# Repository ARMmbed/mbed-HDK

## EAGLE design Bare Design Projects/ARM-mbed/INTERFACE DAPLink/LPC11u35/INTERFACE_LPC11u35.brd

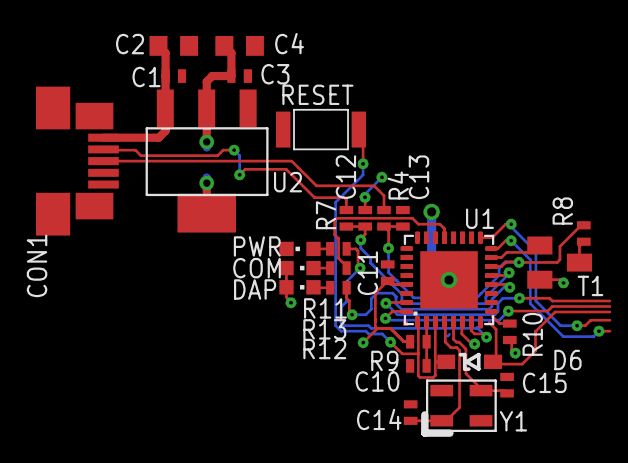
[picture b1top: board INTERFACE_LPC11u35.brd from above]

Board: 2 copper layers, 28 parts (0 on the bottom side), 21 nets.

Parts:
C1, C3, C10, C11: 100nF; 0402
C2, C4: 10uF; 0603
C12, C13, C14, C15: 18pF; 0402
CON1: 47346-0001; USB-MICRO-B-H
D6: BAT60J; SOD323
LED3: RED; CHIPLED_0603
LED4: BLUE; CHIPLED_0603
LED5: GREEN; CHIPLED_0603
R4, R7: 33R; 0402
R8, R12, R13: 1.5K; 0402
R9, R10: 10K; 0402
R11: 470R; 0402
RESET: SKRKAEE010
T1: BSS84; SOT23-3
U1: HVQFN33
U2: TLV1117LV33DCYR; SOT223
Y1: 7M-12.000MAAJ-T; 3.2X.2.5

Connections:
+3.3V: C3.1, C4.1, C11.1, LED4.A, LED5.A, R9.1, R10.1, T1.2, U1.6, U1.29, U2.OUT(1), U2.OUT(2)
GND: C1.2, C2.2, C3.2, C4.2, C10.2, C11.2, C12.2, C13.2, C14.2, C15.2, CON1.GND, LED3.C, RESET.P$1, U1.EXP, U2.GND
HID: R12.2, U1.12
IF_NRESET: C10.1, R9.2, U1.2
ISP: D6.K, RESET.P$2, U1.1, U1.3
MSD: R11.2, U1.7
unnamed: C1.1, C2.1, CON1.VBUS, U2.IN
unnamed: LED3.A, R11.1
unnamed: C13.1, R4.2, R8.2, U1.14
unnamed: C12.1, R7.2, U1.13
unnamed: T1.1, U1.15
unnamed: R8.1, T1.3
unnamed: R10.2, U1.9
unnamed: LED4.C, R12.1
unnamed: LED5.C, R13.1
unnamed: C15.1, U1.5, Y1.P$3
unnamed: C14.1, U1.4, Y1.P$1
TGT_NRESET: D6.A, U1.8
TGT_USB_D+: CON1.D+, R4.1
TGT_USB_D-: CON1.D-, R7.1
UART: R13.2, U1.21

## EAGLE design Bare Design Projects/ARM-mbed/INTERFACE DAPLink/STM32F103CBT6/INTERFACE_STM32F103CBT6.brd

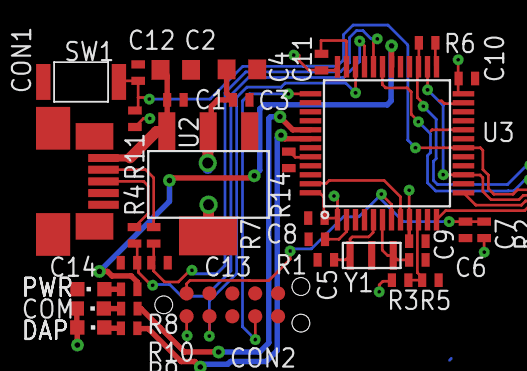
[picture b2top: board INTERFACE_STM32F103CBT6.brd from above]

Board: 2 copper layers, 35 parts (0 on the bottom side), 25 nets.

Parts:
C1, C3, C7, C8, C9, C10, C11, C12: 100nF; 0402
C2, C4: 10uF; 0603
C5, C6: 22pF; 0402
C13, C14: 18pF; 0402
CON1: 47346-0001; USB-MICRO-B-H
CON2: TC2050-IDC-NL
LED1: RED; CHIPLED_0603
LED2: BLUE; CHIPLED_0603
LED3: GREEN; CHIPLED_0603
R1, R11: 10K; 0402
R2, R14: 100K; 0402
R3, R5: 4.7K; 0402
R4, R7: 33R; 0402
R6: 100R; 0402
R8: 470R; 0402
R9, R10: 1.5K; 0402
SW1: SKRKAEE010
U2: TLV1117LV33DCYR; SOT223
U3: STM32F103CBT6; LQFP48
Y1: CSTCE8M00G55-R0

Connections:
+3.3V: C3.1, C4.1, C8.1, C9.1, C10.1, C11.1, CON2.1, LED2.A, LED3.A, R2.1, R3.1, R11.1, U2.OUT(1), U2.OUT(2), U3.1, U3.9, U3.24, U3.36, U3.48
GND: C1.2, C2.2, C3.2, C4.2, C5.2, C6.2, C7.2, C8.2, C9.2, C10.2, C11.2, C12.2, C13.2, C14.2, CON1.GND, CON2.3, CON2.5, LED1.C, R1.1, R5.2, R14.1, SW1.P$2, U2.GND, U3.8, U3.20, U3.23, U3.35, U3.47, Y1.2
IF_NRESET: C7.1, CON2.10, R2.2, U3.7
IF_SWCLK: CON2.4, U3.37
IF_SWDIO: CON2.2, U3.34
unnamed: C1.1, C2.1, CON1.VBUS, U2.IN
unnamed: R8.2, U3.30
unnamed: R14.2, U3.44
unnamed: R1.2, U3.2
unnamed: C6.1, U3.6, Y1.3
unnamed: C5.1, U3.5, Y1.1
unnamed: R3.2, R5.1, U3.10
unnamed: R9.2, U3.42
unnamed: R10.2, U3.41
unnamed: LED1.A, R8.1
unnamed: R6.1, U3.25
unnamed: LED2.C, R9.1
unnamed: LED3.C, R10.1
unnamed: C14.1, R4.1, U3.33
unnamed: C13.1, R7.1, U3.32
TGT_NRESET: C12.1, R11.2, SW1.P$1, U3.18
TGT_SWCLK: U3.15, U3.26
TGT_SWDIO: R6.2, U3.27
TGT_USB_D+: CON1.D+, R4.2
TGT_USB_D-: CON1.D-, R7.2

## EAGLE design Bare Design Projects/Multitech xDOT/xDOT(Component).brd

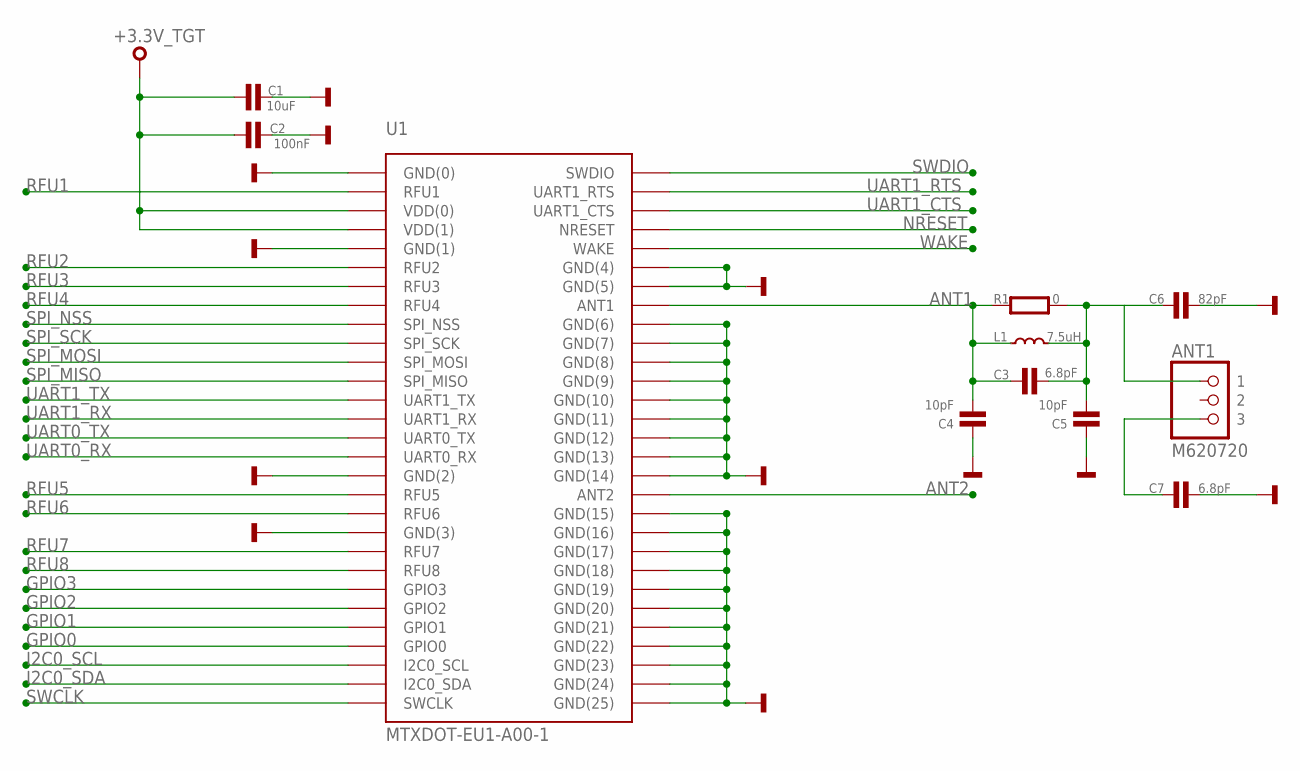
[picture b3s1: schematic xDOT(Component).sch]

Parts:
ANT1: M620720
C1: 10uF; 0603
C2: 100nF; 0603
C3, C7: 6.8pF; 0402
C4, C5: 10pF; 0402
C6: 82pF; 0402
L1: 7.5uH; 0402
R1: 0; 0402
U1: MTXDOT-EU1-A00-1; MTXDOT-EU1/NA1-A00-1

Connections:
+3.3V_TGT: C1.1, C2.1, U1.P$3 (VDD(0)), U1.P$4 (VDD(1))
ANT1: C3.1, C4.2, L1.1, R1.1, U1.P$37 (ANT1)
ANT2: U1.P$47 (ANT2)
GND: C1.2, C2.2, C4.1, C5.1, C6.1, C7.1, U1.P$1 (GND(0)), U1.P$5 (GND(1)), U1.P$17 (GND(2)), U1.P$20 (GND(3)), U1.P$35 (GND(4)), U1.P$36 (GND(5)), U1.P$38 (GND(6)), U1.P$39 (GND(7)), U1.P$40 (GND(8)), U1.P$41 (GND(9)), U1.P$42 (GND(10)), U1.P$43 (GND(11)), U1.P$44 (GND(12)), U1.P$45 (GND(13)), U1.P$46 (GND(14)), U1.P$48 (GND(15)), U1.P$49 (GND(16)), U1.P$50 (GND(17)), U1.P$51 (GND(18)), U1.P$52 (GND(19)), U1.P$53 (GND(20)), U1.P$54 (GND(21)), U1.P$55 (GND(22)), U1.P$56 (GND(23)), U1.P$57 (GND(24)), U1.P$58 (GND(25))
GPIO0: U1.P$26 (GPIO0)
GPIO1: U1.P$25 (GPIO1)
GPIO2: U1.P$24 (GPIO2)
GPIO3: U1.P$23 (GPIO3)
I2C0_SCL: U1.P$27 (I2C0_SCL)
I2C0_SDA: U1.P$28 (I2C0_SDA)
unnamed: ANT1.P$3 (3), C7.2
unnamed: ANT1.P$1 (1), C3.2, C5.2, C6.2, L1.2, R1.2
NRESET: U1.P$33 (NRESET)
RFU1: U1.P$2 (RFU1)
RFU2: U1.P$6 (RFU2)
RFU3: U1.P$7 (RFU3)
RFU4: U1.P$8 (RFU4)
RFU5: U1.P$18 (RFU5)
RFU6: U1.P$19 (RFU6)
RFU7: U1.P$21 (RFU7)
RFU8: U1.P$22 (RFU8)
SPI_MISO: U1.P$12 (SPI_MISO)
SPI_MOSI: U1.P$11 (SPI_MOSI)
SPI_NSS: U1.P$9 (SPI_NSS)
SPI_SCK: U1.P$10 (SPI_SCK)
SWCLK: U1.P$29 (SWCLK)
SWDIO: U1.P$30 (SWDIO)
UART0_RX: U1.P$16 (UART0_RX)
UART0_TX: U1.P$15 (UART0_TX)
UART1_CTS: U1.P$32 (UART1_CTS)
UART1_RTS: U1.P$31 (UART1_RTS)
UART1_RX: U1.P$14 (UART1_RX)
UART1_TX: U1.P$13 (UART1_TX)
WAKE: U1.P$34 (WAKE)

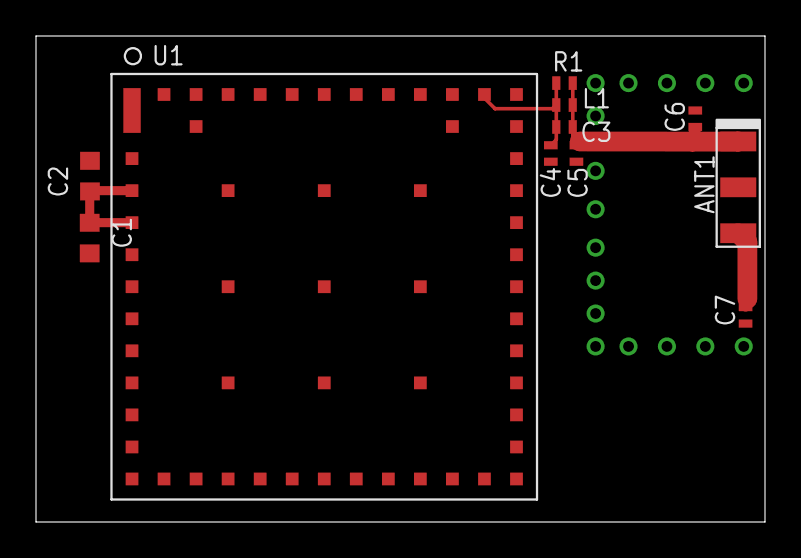
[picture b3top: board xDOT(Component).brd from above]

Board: 2 copper layers, 40.5 x 27.0 mm, 11 parts (0 on the bottom side), 5 nets.

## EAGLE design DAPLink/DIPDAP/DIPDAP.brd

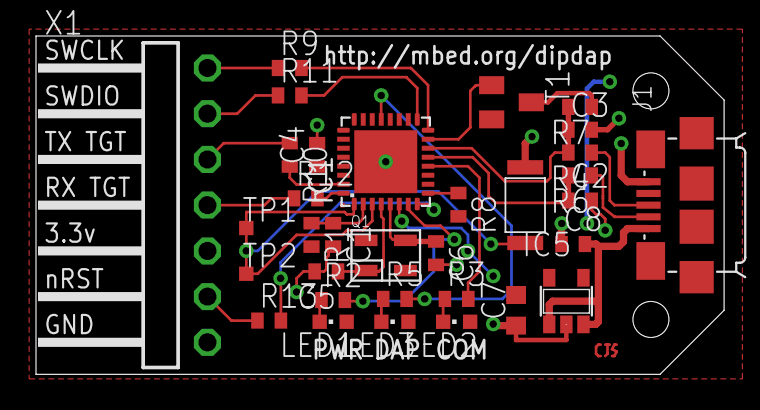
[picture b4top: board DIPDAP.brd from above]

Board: 2 copper layers, 38.2 x 18.8 mm, 33 parts (0 on the bottom side), 30 nets.

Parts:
C1, C4: 100nF; 0402
C2, C3, C5, C6: 18pF; 0402
C7: 10uF; 0603
C8: 1uF; 0402
IC1: HVQFN33
IC5: SOT23-5
J1: ZX62-B-5PA; ZX62-B-5PA(11)
LED1, LED2, LED3: RED; CHIPLED_0603
Q1: 12MHz; 3.2X.2.5
R1, R8: 10k; 0402
R2, R3, R5, R9, R10, R11, R12, R13: 470R; 0402
R4, R6: 33R; 0402
R7: 1k5; 0402
SW1: SPST_SKRKAWW010; SKRKAEE010
T1: BSS84; SOT23
TP1, TP2: TPTP08SQ; TP08SQ
X1: TSW-107-02-S-S-MBED; TSW-107-02-S-S-RA-MBED

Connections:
+3,3V: C4.1, C7.2, IC1.6, IC1.29, IC5.5, LED1.A, LED2.A, LED3.A, R1.2, R8.2, T1.2, X1.3
GND: C1.2, C2.2, C3.2, C4.2, C5.2, C6.2, C7.1, C8.1, IC1.EXP, IC5.2, J1.5, SW1.P$1, X1.1
HID: IC1.12, R3.2
IF_NRESET: C1.1, IC1.2, R1.1
ISP: IC1.1, IC1.3, SW1.P$2, TP1.TP, TP2.TP
MSD: IC1.7, R2.2
unnamed: C3.1, IC1.14, R4.2, R7.2
unnamed: C2.1, IC1.13, R6.2
unnamed: J1.2, R6.1
unnamed: J1.3, R4.1
unnamed: LED1.C, R2.1
unnamed: R7.1, T1.3
unnamed: IC1.9, R8.1
unnamed: LED2.C, R3.1
unnamed: LED3.C, R5.1
unnamed: C6.1, IC1.5, Q1.P$3
unnamed: C5.1, IC1.4, Q1.P$1
unnamed: IC1.15, T1.1
unnamed: IC1.32, R12.2
unnamed: IC1.31, R10.2
TGT_NRESET: IC1.8, R13.2
TGT_NRESET_BUF: R13.1, X1.2
TGT_RX: R12.1, X1.4
TGT_SWCLK: IC1.16, R9.2
TGT_SWCLK_BUF: R9.1, X1.7
TGT_SWDIO: IC1.17, R11.2
TGT_SWDIO_BUF: R11.1, X1.6
TGT_TX: R10.1, X1.5
UART: IC1.21, R5.2
VBUS: C8.2, IC5.1, IC5.3, J1.1

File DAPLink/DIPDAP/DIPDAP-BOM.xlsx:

Assembly | variant:
Part | Value | Device | Package | Description | Mfg | MfgPn | Disti | Order
C1 | 100nF | C0402 | 402 | Capacitor | MULTICOMP | MC0402X104K100CT | Farnell | 1759380
C2 | 18pF | C0402 | 402 | Capacitor | MULTICOMP | MC0402N180J500CT | Farnell | 1758947
C3 | 18pF | C0402 | 402 | Capacitor | MULTICOMP | MC0402N180J500CT | Farnell | 1758947
C4 | 100nF | C0402 | 402 | Capacitor | MULTICOMP | MC0402X104K100CT | Farnell | 1759380
C5 | 18pF | C0402 | 402 | Capacitor | MULTICOMP | MC0402N180J500CT | Farnell | 1758947
C6 | 18pF | C0402 | 402 | Capacitor | MULTICOMP | MC0402N180J500CT | Farnell | 1758947
C7 | 10uF | C0603 | 603 | Capacitor | MULTICOMP | MCCA000517 | Farnell | 1759393
C8 | 1uF | C0402 | 402 | Capacitor | MULTICOMP | MCCA000506 | Farnell | 1759381
IC1 | IF-LPC11U35 | HVQFN33 | NXP | LPC11U35FHI33/501 |  |  | Farnell | 2115658
IC5 | TC1014 | SOT23-5 | MICROCHIP | TC1014-3.3VCT713 |  |  | Farnell | 1331502
J1 | ZX62-B-5PA | ZX62-B-5PA | ZX62-B-5PA(11) | Hirose | ZX62-B-5PA(11) |  | Farnell | 1645325
LED1 | RED | LED0603 | CHIPLED_0603 | SMD | LED | KP-1608SURCK | Farnell | 2290329
LED2 | RED | LED0603 | CHIPLED_0603 | SMD | LED | KP-1608SURCK | Farnell | 2290329
LED3 | RED | LED0603 | CHIPLED_0603 | SMD | LED | KP-1608SURCK | Farnell | 2290329
Q1 | 12MHz | Q_3.2X2.5 | 3.2X.2.5 | TXC | 7M-12.000MAAJ-T |  | Farnell | 1842056
R1 | 10k | R0402 | 402 | Resistor | MULTICOMP | MCMR04X103-JTL | Farnell | 2072528
R2 | 470R | R0402 | 402 | Resistor | MULTICOMP | MCMR04X471-JTL | Farnell | 2073068
R3 | 470R | R0402 | 402 | Resistor | MULTICOMP | MCMR04X471-JTL | Farnell | 2073068
R4 | 33R | R0402 | 402 | Resistor | MULTICOMP | MCMR04X330-JTL | Farnell | 2072926
R5 | 470R | R0402 | 402 | Resistor | MULTICOMP | MCMR04X471-JTL | Farnell | 2073068
R6 | 33R | R0402 | 402 | Resistor | MULTICOMP | MCMR04X330-JTL | Farnell | 2072926
R7 | 1k5 | R0402 | 402 | Resistor | MULTICOMP | MCMR04X152-JTL | Farnell | 2072650
R8 | 10k | R0402 | 402 | Resistor | MULTICOMP | MCMR04X103-JTL | Farnell | 2072528
R9 | 470R | R0402 | 402 | Resistor | MULTICOMP | MCMR04X471-JTL | Farnell | 2073068
R10 | 470R | R0402 | 402 | Resistor | MULTICOMP | MCMR04X471-JTL | Farnell | 2073068
R11 | 470R | R0402 | 402 | Resistor | MULTICOMP | MCMR04X471-JTL | Farnell | 2073068
R12 | 470R | R0402 | 402 | Resistor | MULTICOMP | MCMR04X471-JTL | Farnell | 2073068
R13 | 470R | R0402 | 402 | Resistor | MULTICOMP | MCMR04X471-JTL | Farnell | 2073068
SW1 | SPST_SKRKAWW010 | SPST_SKRKAWW010 | SKRKAEE010 | Resistor | Alps | SKRKAEE010 | Mouser | 688-SKRKAE
T1 | BSS84 | BSS84 | SOT23 | P-CHANNEL | Infineon | BSS84P | Farnell | 1056526
X1 | TSW-107-02-S-S | TSW-107-02-S-S | TSW-107-02-S-S-RA | THROUGH-HOLE

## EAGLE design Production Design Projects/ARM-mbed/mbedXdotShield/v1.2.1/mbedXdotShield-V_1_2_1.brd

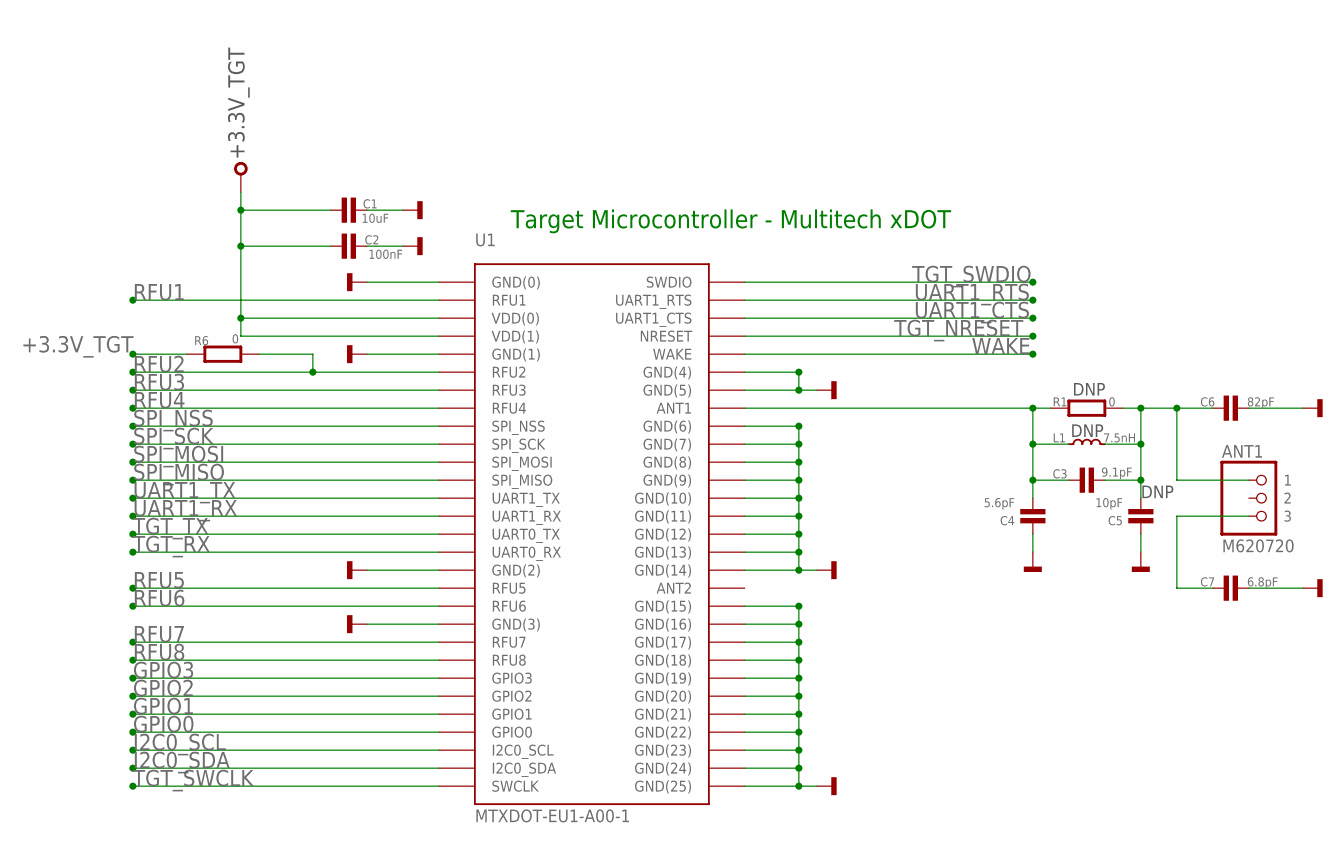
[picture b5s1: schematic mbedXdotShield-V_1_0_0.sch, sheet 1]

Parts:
ANT1: M620720
C1: 10uF; 0603
C2: 100nF; 0603
C3: 9.1pF; 0402
C4: 5.6pF; 0402
C5: 10pF; 0402
C6: 82pF; 0402
C7: 6.8pF; 0402
L1: 7.5nH; 0402
R1, R6: 0; 0402
U1: MTXDOT-EU1-A00-1; MTXDOT-EU1/NA1-A00-1

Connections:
ANT1: C3.1, C4.2, L1.1, R1.1, U1.P$37 (ANT1)
GND: C1.2, C2.2, C4.1, C5.1, C6.1, C7.1, U1.P$1 (GND(0)), U1.P$5 (GND(1)), U1.P$17 (GND(2)), U1.P$20 (GND(3)), U1.P$35 (GND(4)), U1.P$36 (GND(5)), U1.P$38 (GND(6)), U1.P$39 (GND(7)), U1.P$40 (GND(8)), U1.P$41 (GND(9)), U1.P$42 (GND(10)), U1.P$43 (GND(11)), U1.P$44 (GND(12)), U1.P$45 (GND(13)), U1.P$46 (GND(14)), U1.P$48 (GND(15)), U1.P$49 (GND(16)), U1.P$50 (GND(17)), U1.P$51 (GND(18)), U1.P$52 (GND(19)), U1.P$53 (GND(20)), U1.P$54 (GND(21)), U1.P$55 (GND(22)), U1.P$56 (GND(23)), U1.P$57 (GND(24)), U1.P$58 (GND(25)); also elsewhere on the board
GPIO0: U1.P$26 (GPIO0); also elsewhere on the board
GPIO1: U1.P$25 (GPIO1); also elsewhere on the board
GPIO2: U1.P$24 (GPIO2); also elsewhere on the board
GPIO3: U1.P$23 (GPIO3); also elsewhere on the board
I2C0_SCL: U1.P$27 (I2C0_SCL); also elsewhere on the board
I2C0_SDA: U1.P$28 (I2C0_SDA); also elsewhere on the board
unnamed: ANT1.P$3 (3), C7.2
unnamed: ANT1.P$1 (1), C3.2, C5.2, C6.2, L1.2, R1.2
RFU1: U1.P$2 (RFU1)
RFU2: R6.2, U1.P$6 (RFU2)
RFU3: U1.P$7 (RFU3)
RFU4: U1.P$8 (RFU4)
RFU5: U1.P$18 (RFU5)
RFU6: U1.P$19 (RFU6)
RFU7: U1.P$21 (RFU7)
RFU8: U1.P$22 (RFU8)
SPI_MISO: U1.P$12 (SPI_MISO); also elsewhere on the board
SPI_MOSI: U1.P$11 (SPI_MOSI); also elsewhere on the board
SPI_NSS: U1.P$9 (SPI_NSS); also elsewhere on the board
SPI_SCK: U1.P$10 (SPI_SCK); also elsewhere on the board
TGT_NRESET: U1.P$33 (NRESET); also elsewhere on the board
TGT_RX: U1.P$16 (UART0_RX); also elsewhere on the board
TGT_SWCLK: U1.P$29 (SWCLK); also elsewhere on the board
TGT_SWDIO: U1.P$30 (SWDIO); also elsewhere on the board
TGT_TX: U1.P$15 (UART0_TX); also elsewhere on the board
UART1_CTS: U1.P$32 (UART1_CTS); also elsewhere on the board
UART1_RTS: U1.P$31 (UART1_RTS); also elsewhere on the board
UART1_RX: U1.P$14 (UART1_RX); also elsewhere on the board
UART1_TX: U1.P$13 (UART1_TX); also elsewhere on the board
WAKE: U1.P$34 (WAKE); also elsewhere on the board

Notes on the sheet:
Target Microcontroller - Multitech xDOT
DNP

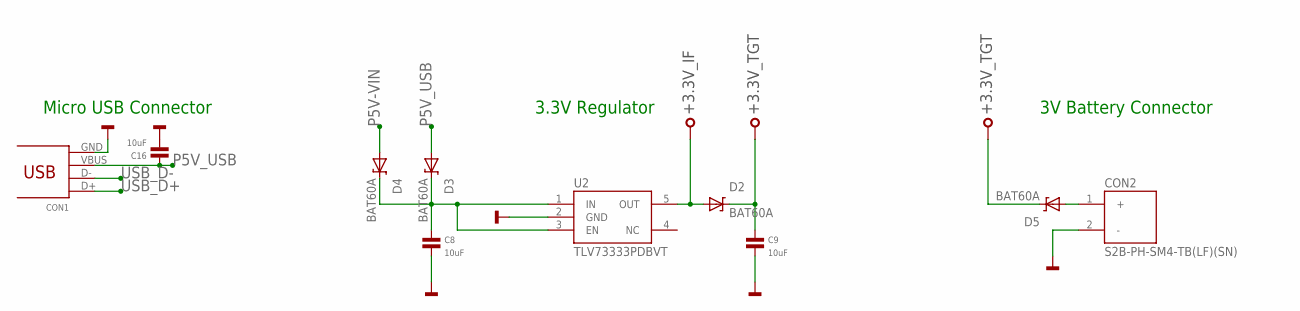
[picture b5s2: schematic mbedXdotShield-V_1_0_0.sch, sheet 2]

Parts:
C8, C9, C16: 10uF; 0603
CON1: 47346-0001; USB-MICRO-B-H
CON2: S2B-PH-SM4-TB(LF)(SN)
D2, D3, D4, D5: BAT60A; SOD323
U2: TLV73333PDBVT; SOT23-5

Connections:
GND: C8.2, C9.2, C16.2, CON1.GND, CON2.2 (-), U2.2 (GND); also elsewhere on the board
P5V-VIN: D4.A; also elsewhere on the board
P5V_USB: C16.1, CON1.VBUS, D3.A; also elsewhere on the board
USB_D+: CON1.D+; also elsewhere on the board
USB_D-: CON1.D-; also elsewhere on the board

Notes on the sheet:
3.3V Regulator
Micro USB Connector
3V Battery Connector

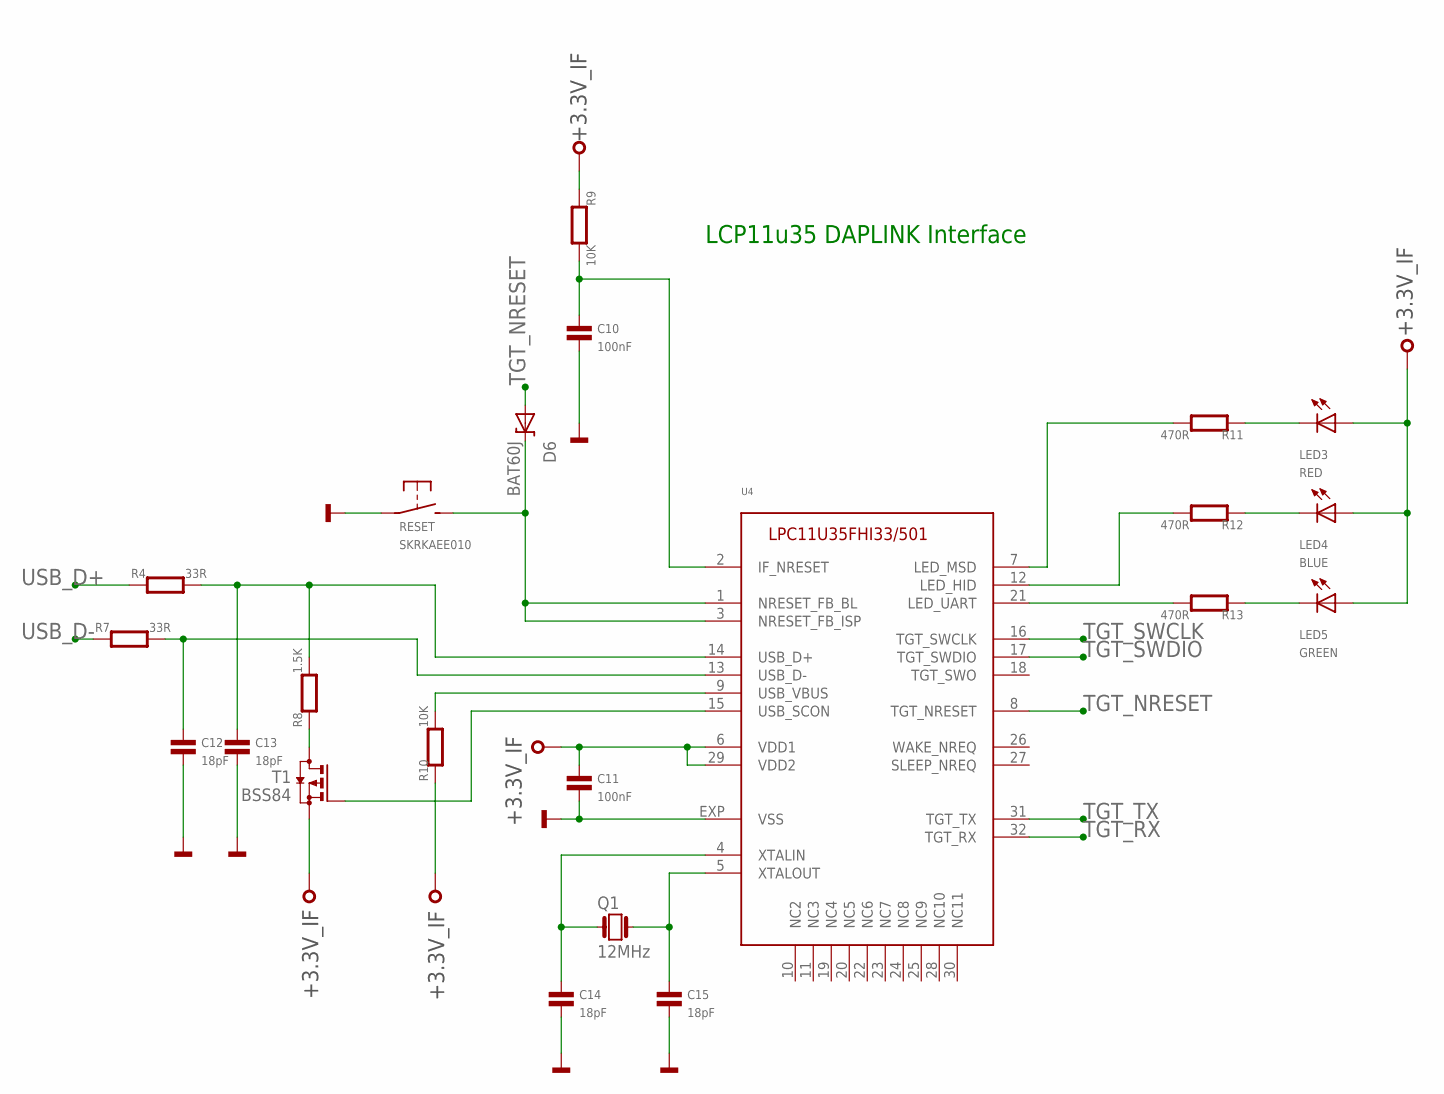
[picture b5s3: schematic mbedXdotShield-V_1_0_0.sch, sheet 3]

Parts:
C10, C11: 100nF; 0402
C12, C13, C14, C15: 18pF; 0402
D6: BAT60J; SOD323
LED3: RED; CHIPLED_0603
LED4: BLUE; CHIPLED_0603
LED5: GREEN; CHIPLED_0603
Q1: 12MHz; 3.2X.2.5
R4, R7: 33R; 0402
R8: 1.5K; 0402
R9, R10: 10K; 0402
R11, R12, R13: 470R; 0402
RESET: SKRKAEE010
T1: BSS84; SOT23-3
U4: IF-LPC11U35; HVQFN33

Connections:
GND: C10.2, C11.2, C12.2, C13.2, C14.2, C15.2, RESET.P$1, U4.EXP (VSS); also elsewhere on the board
HID: R12.2, U4.12 (LED_HID)
IF_NRESET: C10.1, R9.2, U4.2 (IF_NRESET)
ISP: D6.K, RESET.P$2 (S), U4.1 (NRESET_FB_BL), U4.3 (NRESET_FB_ISP)
MSD: R11.2, U4.7 (LED_MSD)
unnamed: C13.1, R4.2, R8.2, U4.14 (USB_D+)
unnamed: C12.1, R7.2, U4.13 (USB_D-)
unnamed: T1.1 (G), U4.15 (USB_SCON)
unnamed: R8.1, T1.3 (D)
unnamed: R10.2, U4.9 (USB_VBUS)
unnamed: LED3.C, R11.1
unnamed: LED4.C, R12.1
unnamed: LED5.C, R13.1
unnamed: C15.1, Q1.P$3 (2), U4.5 (XTALOUT)
unnamed: C14.1, Q1.P$1 (1), U4.4 (XTALIN)
TGT_NRESET: D6.A, U4.8 (TGT_NRESET); also elsewhere on the board
TGT_RX: U4.32 (TGT_RX); also elsewhere on the board
TGT_SWCLK: U4.16 (TGT_SWCLK); also elsewhere on the board
TGT_SWDIO: U4.17 (TGT_SWDIO); also elsewhere on the board
TGT_TX: U4.31 (TGT_TX); also elsewhere on the board
UART: R13.2, U4.21 (LED_UART)
USB_D+: R4.1; also elsewhere on the board
USB_D-: R7.1; also elsewhere on the board

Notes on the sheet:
LCP11u35 DAPLINK Interface

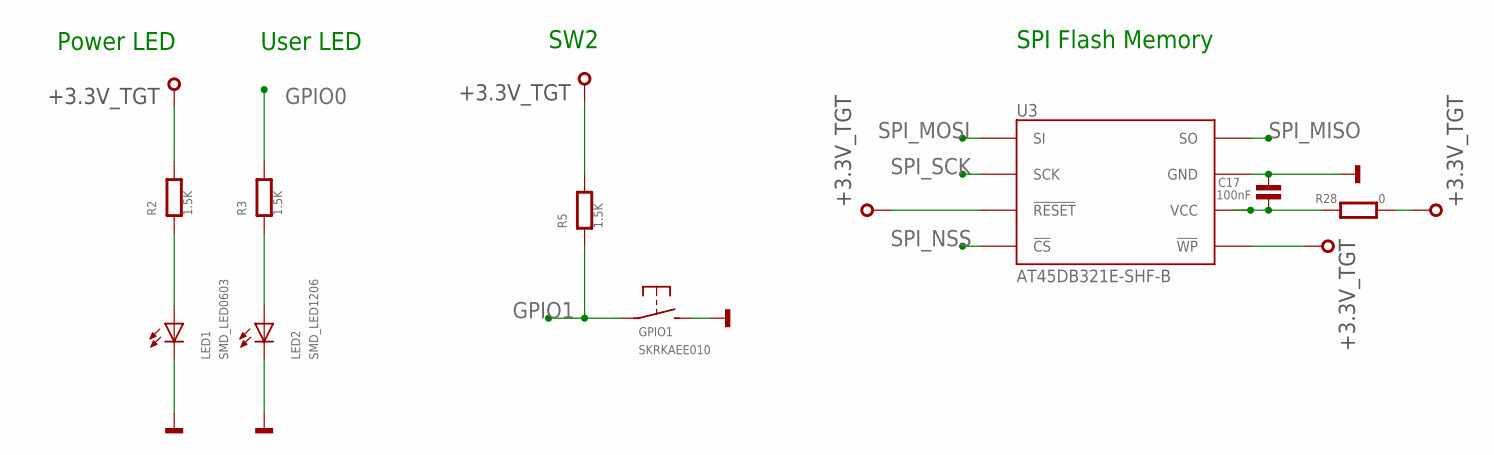
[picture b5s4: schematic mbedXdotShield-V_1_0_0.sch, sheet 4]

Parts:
C17: 100nF; 0603
GPIO1: SKRKAEE010
LED1: SMD_LED0603; CHIPLED_0603
LED2: SMD_LED1206; CHIPLED_1206
R2, R3, R5: 1.5K; 0402
R28: 0; 0402
U3: AT45DB321E-SHF-B; SO8

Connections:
GND: C17.1, GPIO1.P$2 (S), LED1.C, LED2.C, U3.7 (GND); also elsewhere on the board
GPIO0: R3.2; also elsewhere on the board
GPIO1: GPIO1.P$1, R5.1; also elsewhere on the board
unnamed: LED2.A, R3.1
unnamed: LED1.A, R2.1
unnamed: C17.2, R28.1, U3.6 (VCC)
SPI_MISO: U3.8 (SO); also elsewhere on the board
SPI_MOSI: U3.1 (SI); also elsewhere on the board
SPI_NSS: U3.4 (!CS); also elsewhere on the board
SPI_SCK: U3.2 (SCK); also elsewhere on the board

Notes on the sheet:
SW2
Power LED
User LED
SPI Flash Memory

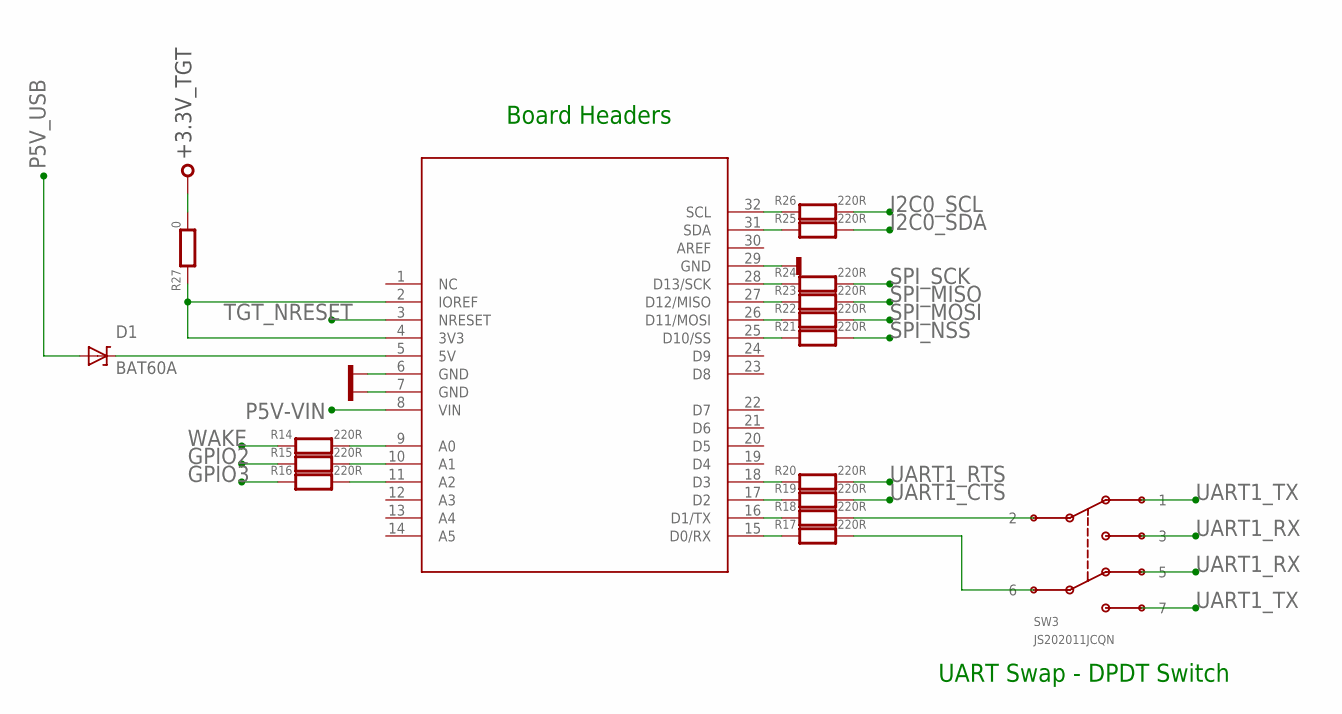
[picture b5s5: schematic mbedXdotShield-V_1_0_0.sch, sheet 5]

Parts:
BRD1: K64F/K22F-SHIELD; K64F/K22F
D1: BAT60A; SOD323
R14, R15, R16, R17, R18, R19, R20, R21, R22, R23, R24, R25, R26: 220R; 0402
R27: 0; 0402
SW3: JS202011JCQN

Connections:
GND: BRD1.6 (GND), BRD1.7 (GND), BRD1.29 (GND); also elsewhere on the board
GPIO2: R15.1; also elsewhere on the board
GPIO3: R16.1; also elsewhere on the board
I2C0_SCL: R26.2; also elsewhere on the board
I2C0_SDA: R25.2; also elsewhere on the board
unnamed: BRD1.9 (A0), R14.2
unnamed: BRD1.10 (A1), R15.2
unnamed: BRD1.11 (A2), R16.2
unnamed: BRD1.15 (D0/RX), R17.1
unnamed: BRD1.16 (D1/TX), R18.1
unnamed: BRD1.17 (D2), R19.1
unnamed: BRD1.5 (5V), D1.K
unnamed: BRD1.18 (D3), R20.1
unnamed: BRD1.25 (D10/SS), R21.1
unnamed: BRD1.26 (D11/MOSI), R22.1
unnamed: BRD1.27 (D12/MISO), R23.1
unnamed: BRD1.28 (D13/SCK), R24.1
unnamed: BRD1.31 (SDA), R25.1
unnamed: BRD1.32 (SCL), R26.1
unnamed: BRD1.2 (IOREF), BRD1.4 (3V3), R27.1
unnamed: R17.2, SW3.6
unnamed: R18.2, SW3.2
P5V-VIN: BRD1.8 (VIN); also elsewhere on the board
P5V_USB: D1.A; also elsewhere on the board
SPI_MISO: R23.2; also elsewhere on the board
SPI_MOSI: R22.2; also elsewhere on the board
SPI_NSS: R21.2; also elsewhere on the board
SPI_SCK: R24.2; also elsewhere on the board
TGT_NRESET: BRD1.3 (NRESET); also elsewhere on the board
UART1_CTS: R19.2; also elsewhere on the board
UART1_RTS: R20.2; also elsewhere on the board
UART1_RX: SW3.3, SW3.5; also elsewhere on the board
UART1_TX: SW3.1, SW3.7; also elsewhere on the board
WAKE: R14.1; also elsewhere on the board

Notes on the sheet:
Board Headers
UART Swap - DPDT Switch

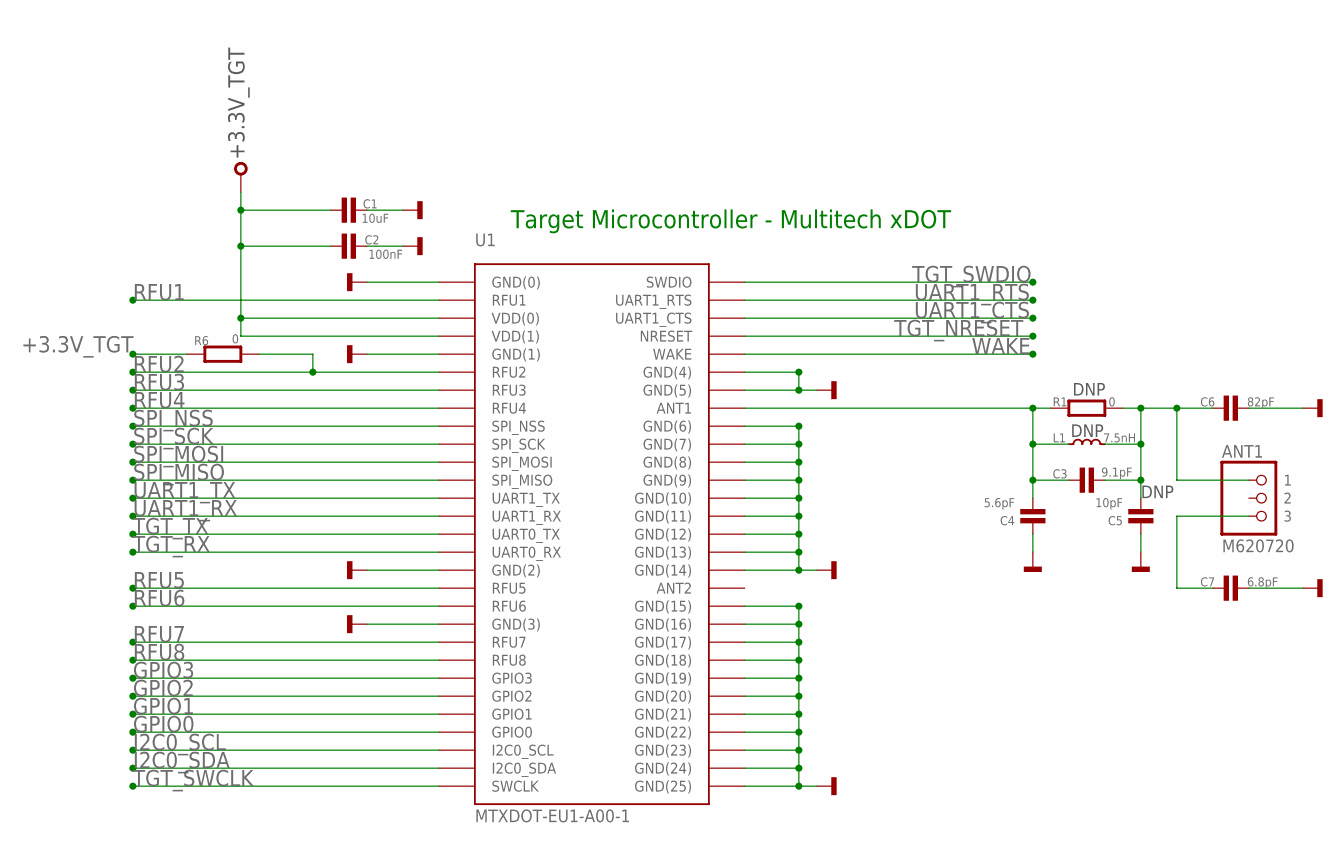
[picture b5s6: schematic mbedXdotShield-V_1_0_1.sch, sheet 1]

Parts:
ANT1: M620720
C1: 10uF; 0603
C2: 100nF; 0603
C3: 9.1pF; 0402
C4: 5.6pF; 0402
C5: 10pF; 0402
C6: 82pF; 0402
C7: 6.8pF; 0402
L1: 7.5nH; 0402
R1, R6: 0; 0402
U1: MTXDOT-EU1-A00-1; MTXDOT-EU1/NA1-A00-1

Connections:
ANT1: C3.1, C4.2, L1.1, R1.1, U1.P$37 (ANT1)
GND: C1.2, C2.2, C4.1, C5.1, C6.1, C7.1, U1.P$1 (GND(0)), U1.P$5 (GND(1)), U1.P$17 (GND(2)), U1.P$20 (GND(3)), U1.P$35 (GND(4)), U1.P$36 (GND(5)), U1.P$38 (GND(6)), U1.P$39 (GND(7)), U1.P$40 (GND(8)), U1.P$41 (GND(9)), U1.P$42 (GND(10)), U1.P$43 (GND(11)), U1.P$44 (GND(12)), U1.P$45 (GND(13)), U1.P$46 (GND(14)), U1.P$48 (GND(15)), U1.P$49 (GND(16)), U1.P$50 (GND(17)), U1.P$51 (GND(18)), U1.P$52 (GND(19)), U1.P$53 (GND(20)), U1.P$54 (GND(21)), U1.P$55 (GND(22)), U1.P$56 (GND(23)), U1.P$57 (GND(24)), U1.P$58 (GND(25)); also elsewhere on the board
GPIO0: U1.P$26 (GPIO0); also elsewhere on the board
GPIO1: U1.P$25 (GPIO1); also elsewhere on the board
GPIO2: U1.P$24 (GPIO2); also elsewhere on the board
GPIO3: U1.P$23 (GPIO3); also elsewhere on the board
I2C0_SCL: U1.P$27 (I2C0_SCL); also elsewhere on the board
I2C0_SDA: U1.P$28 (I2C0_SDA); also elsewhere on the board
unnamed: ANT1.P$3 (3), C7.2
unnamed: ANT1.P$1 (1), C3.2, C5.2, C6.2, L1.2, R1.2
RFU1: U1.P$2 (RFU1)
RFU2: R6.2, U1.P$6 (RFU2)
RFU3: U1.P$7 (RFU3)
RFU4: U1.P$8 (RFU4)
RFU5: U1.P$18 (RFU5)
RFU6: U1.P$19 (RFU6)
RFU7: U1.P$21 (RFU7)
RFU8: U1.P$22 (RFU8)
SPI_MISO: U1.P$12 (SPI_MISO); also elsewhere on the board
SPI_MOSI: U1.P$11 (SPI_MOSI); also elsewhere on the board
SPI_NSS: U1.P$9 (SPI_NSS); also elsewhere on the board
SPI_SCK: U1.P$10 (SPI_SCK); also elsewhere on the board
TGT_NRESET: U1.P$33 (NRESET); also elsewhere on the board
TGT_RX: U1.P$16 (UART0_RX); also elsewhere on the board
TGT_SWCLK: U1.P$29 (SWCLK); also elsewhere on the board
TGT_SWDIO: U1.P$30 (SWDIO); also elsewhere on the board
TGT_TX: U1.P$15 (UART0_TX); also elsewhere on the board
UART1_CTS: U1.P$32 (UART1_CTS); also elsewhere on the board
UART1_RTS: U1.P$31 (UART1_RTS); also elsewhere on the board
UART1_RX: U1.P$14 (UART1_RX); also elsewhere on the board
UART1_TX: U1.P$13 (UART1_TX); also elsewhere on the board
WAKE: U1.P$34 (WAKE); also elsewhere on the board

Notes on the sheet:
Target Microcontroller - Multitech xDOT
DNP

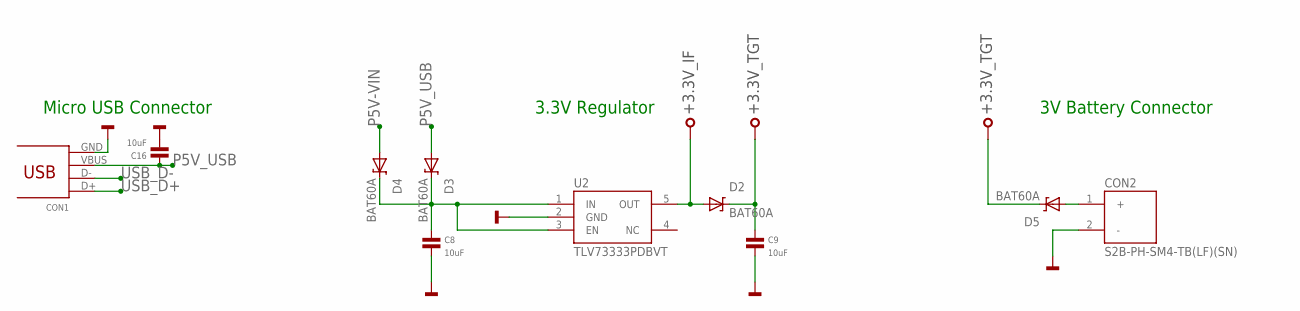
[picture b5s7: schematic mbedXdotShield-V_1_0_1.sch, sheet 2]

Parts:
C8, C9, C16: 10uF; 0603
CON1: 47346-0001; USB-MICRO-B-H
CON2: S2B-PH-SM4-TB(LF)(SN)
D2, D3, D4, D5: BAT60A; SOD323
U2: TLV73333PDBVT; SOT23-5

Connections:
GND: C8.2, C9.2, C16.2, CON1.GND, CON2.2 (-), U2.2 (GND); also elsewhere on the board
P5V-VIN: D4.A; also elsewhere on the board
P5V_USB: C16.1, CON1.VBUS, D3.A; also elsewhere on the board
USB_D+: CON1.D+; also elsewhere on the board
USB_D-: CON1.D-; also elsewhere on the board

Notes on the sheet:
3.3V Regulator
Micro USB Connector
3V Battery Connector

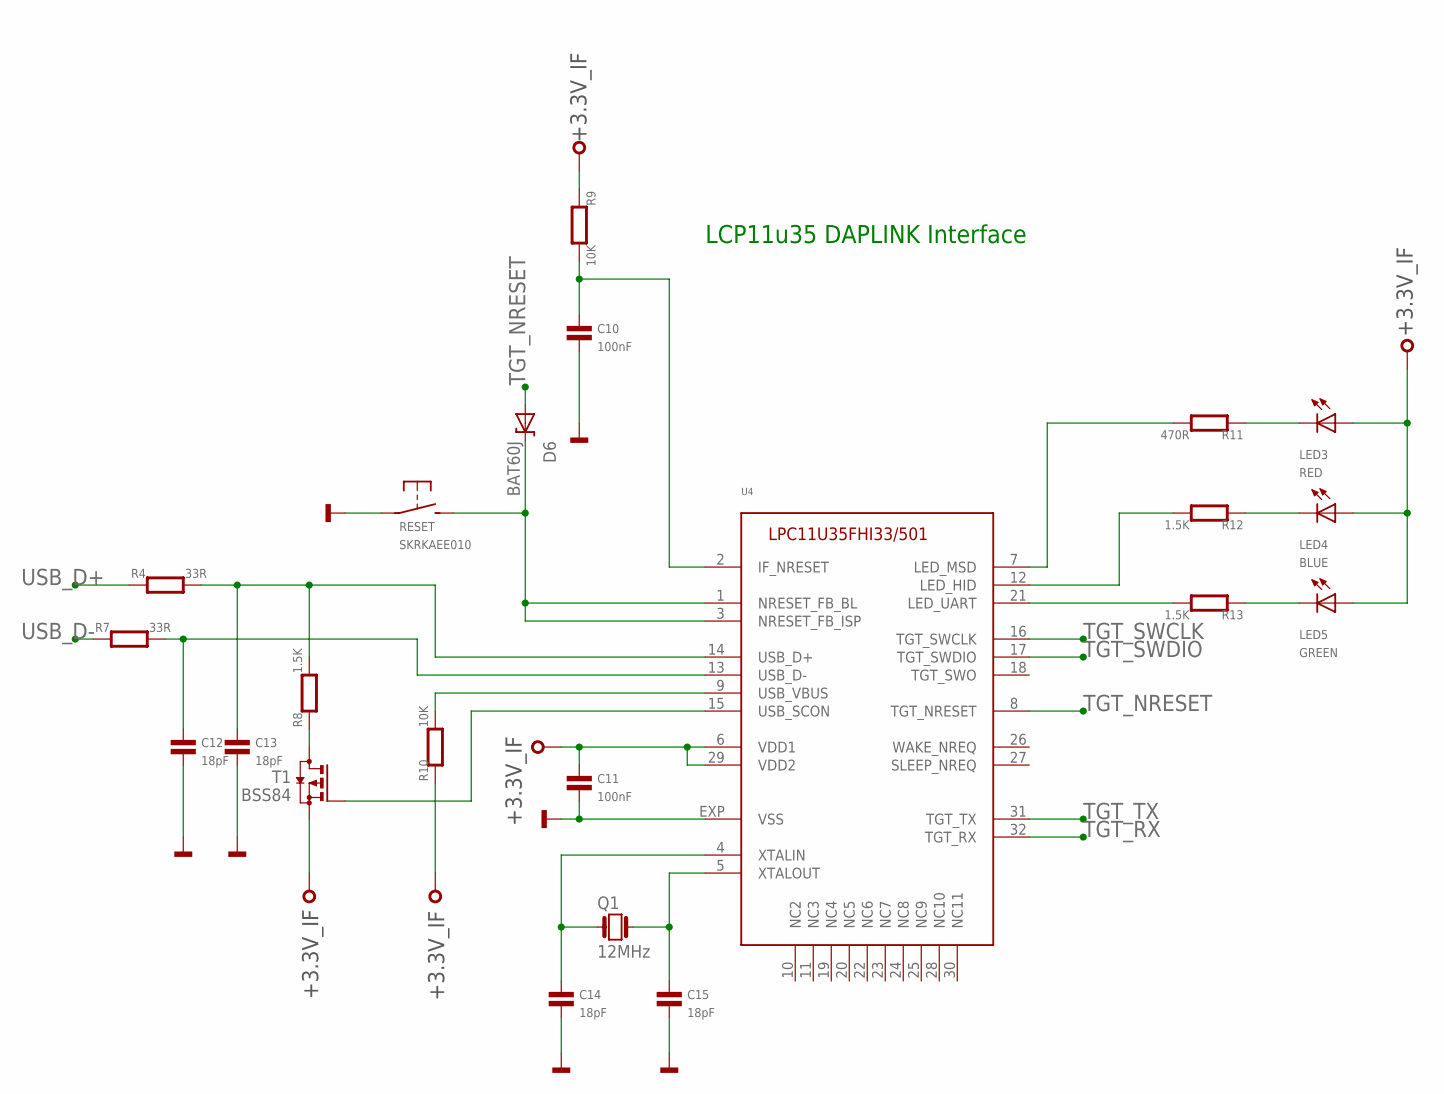
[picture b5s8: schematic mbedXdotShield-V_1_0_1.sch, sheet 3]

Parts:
C10, C11: 100nF; 0402
C12, C13, C14, C15: 18pF; 0402
D6: BAT60J; SOD323
LED3: RED; CHIPLED_0603
LED4: BLUE; CHIPLED_0603
LED5: GREEN; CHIPLED_0603
Q1: 12MHz; 3.2X.2.5
R4, R7: 33R; 0402
R8, R12, R13: 1.5K; 0402
R9, R10: 10K; 0402
R11: 470R; 0402
RESET: SKRKAEE010
T1: BSS84; SOT23-3
U4: IF-LPC11U35; HVQFN33

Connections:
GND: C10.2, C11.2, C12.2, C13.2, C14.2, C15.2, RESET.P$1, U4.EXP (VSS); also elsewhere on the board
HID: R12.2, U4.12 (LED_HID)
IF_NRESET: C10.1, R9.2, U4.2 (IF_NRESET)
ISP: D6.K, RESET.P$2 (S), U4.1 (NRESET_FB_BL), U4.3 (NRESET_FB_ISP)
MSD: R11.2, U4.7 (LED_MSD)
unnamed: C13.1, R4.2, R8.2, U4.14 (USB_D+)
unnamed: C12.1, R7.2, U4.13 (USB_D-)
unnamed: T1.1 (G), U4.15 (USB_SCON)
unnamed: R8.1, T1.3 (D)
unnamed: R10.2, U4.9 (USB_VBUS)
unnamed: LED3.C, R11.1
unnamed: LED4.C, R12.1
unnamed: LED5.C, R13.1
unnamed: C15.1, Q1.P$3 (2), U4.5 (XTALOUT)
unnamed: C14.1, Q1.P$1 (1), U4.4 (XTALIN)
TGT_NRESET: D6.A, U4.8 (TGT_NRESET); also elsewhere on the board
TGT_RX: U4.32 (TGT_RX); also elsewhere on the board
TGT_SWCLK: U4.16 (TGT_SWCLK); also elsewhere on the board
TGT_SWDIO: U4.17 (TGT_SWDIO); also elsewhere on the board
TGT_TX: U4.31 (TGT_TX); also elsewhere on the board
UART: R13.2, U4.21 (LED_UART)
USB_D+: R4.1; also elsewhere on the board
USB_D-: R7.1; also elsewhere on the board

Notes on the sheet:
LCP11u35 DAPLINK Interface

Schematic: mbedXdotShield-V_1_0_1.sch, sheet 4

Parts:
C17: 100nF; 0603
GPIO1: SKRKAEE010
LED1: SMD_LED0603; CHIPLED_0603
LED2: SMD_LED1206; CHIPLED_1206
R2, R5: 1.5K; 0402
R3: 220R; 0402
R28: 0; 0402
U3: AT45DB321E-SHF-B; SO8

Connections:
GND: C17.1, GPIO1.P$2 (S), LED1.C, LED2.C, U3.7 (GND); also elsewhere on the board
GPIO0: R3.2; also elsewhere on the board
GPIO1: GPIO1.P$1, R5.1; also elsewhere on the board
unnamed: LED2.A, R3.1
unnamed: LED1.A, R2.1
unnamed: C17.2, R28.1, U3.6 (VCC)
SPI_MISO: U3.8 (SO); also elsewhere on the board
SPI_MOSI: U3.1 (SI); also elsewhere on the board
SPI_NSS: U3.4 (!CS); also elsewhere on the board
SPI_SCK: U3.2 (SCK); also elsewhere on the board

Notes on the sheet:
SW2
Power LED
User LED
SPI Flash Memory
